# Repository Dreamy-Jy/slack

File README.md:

This is a repo containing all docs related to Slack, a custom plank style keyboard meant for being used while relaxing.

There are 2 prototype revisions planned, each one getting closer to my ideal. Experimental modules will be hosted here as well.

Any revisions pass the second revision will be for refinements.

Why are components rated differently?
- Caps have a voltage rating
- Resistor have a power dissipation rating

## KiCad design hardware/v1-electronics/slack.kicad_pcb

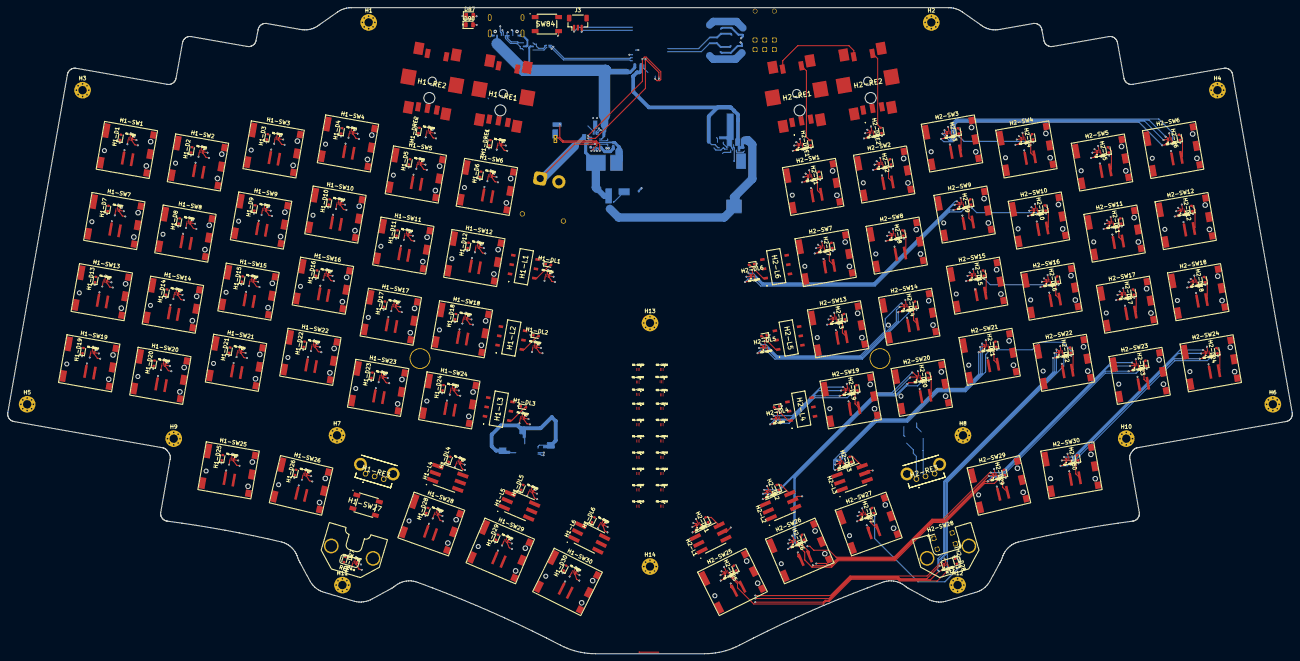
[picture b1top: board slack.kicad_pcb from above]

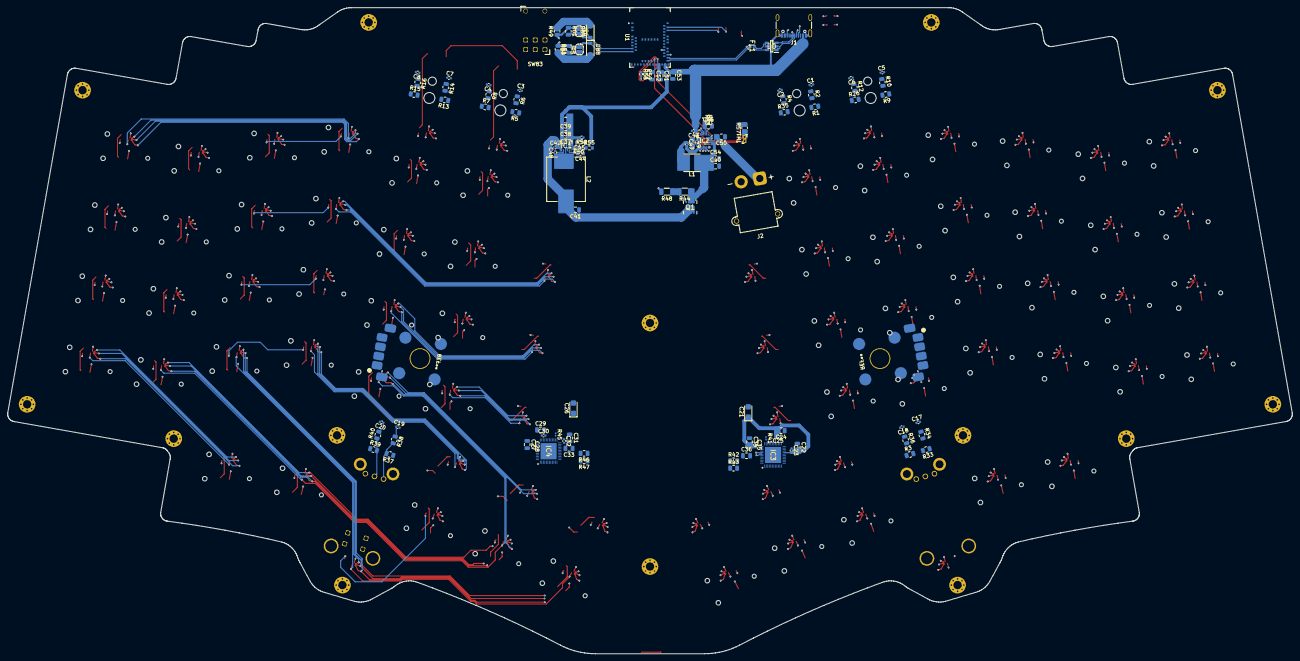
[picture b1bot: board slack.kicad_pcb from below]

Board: 4 copper layers, 338.9 x 170.4 mm, 376 parts (108 on the bottom side), 216 nets.

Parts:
C1, C2, C3, C4, C5, C6, C7, C8, C17, C18, C19, C20: 0.01μF; C_0402_1005Metric
C21, C26: 22μF; CP_EIA-3216-18_Kemet-A
C22, C24, C27, C29, C31, C33, C34, C36: 0.47μF; C_0805_2012Metric
C23, C25, C28, C30, C32, C35, C42, C48: 0.1μF; C_0402_1005Metric
C37, C38, C39, C49: 22μF; C_0805_2012Metric
C40, C41, C50, C51, C52, C53, C54: 10μF; C_0805_2012Metric
C43: 1μF; C_0402_1005Metric
C44: 2.20μF; C_0603_1608Metric
C45: 2.2nF; C_0603_1608Metric
C46: 4.7μF; C_0805_2012Metric
C47: 22nF; C_0402_1005Metric
D0: USBLC6-2SC6; SOT95P280X145-6N
D87, D90: LED_Small_Filled; LED_0805_2012Metric
D88, D89: 3.6V; D_SOD-123
FL1: EXC14CE900U
H1, H2, H3, H4, H5, H6, H7, H8, H9, H10, H11, H12, H13, H14: MountingHole_2.2mm_M2_Pad_Via
H1-D1, H1-D2, H1-D3, H1-D4, H1-D5, H1-D6, H1-D7, H1-D8, H1-D9, H1-D10, H1-D11, H1-D12, H1-D13, H1-D14, H1-D15, H1-D16, H1-D17, H1-D18, H1-D19, H1-D20, H1-D21, H1-D22, H1-D23, H1-D24, H1-D25, H1-D26, H1-D27, H1-D28, H1-D29, H1-D30, H1-DL1, H1-DL2, H1-DL3, H1-DL4, H1-DL5, H1-DL6, H1-DRE1, H1-DRE2, H2-D1, H2-D2, H2-D3, H2-D4, H2-D5, H2-D6, H2-D7, H2-D8, H2-D9, H2-D10, H2-D11, H2-D12, H2-D13, H2-D14, H2-D15, H2-D16, H2-D17, H2-D18, H2-D19, H2-D20, H2-D21, H2-D22, H2-D23, H2-D24, H2-D25, H2-D26, H2-D27, H2-D28, H2-D29, H2-D30, H2-DL1, H2-DL2, H2-DL3, H2-DL4, H2-DL5, H2-DL6, H2-DRE1, H2-DRE2: BAS16TS; D_SOD-523
H1-L1, H1-L2, H1-L3, H2-L4, H2-L5, H2-L6: SS-3235S-L3; SS3235SL3
H1-L4, H1-L5, H1-L6, H2-L1, H2-L2, H2-L3: BTSA-L-S-8
H1-LED1, H1-LED2, H1-LED3, H1-LED4, H1-LED5, H1-LED6, H1-LED7, H1-LED8, H1-LED9, H1-LED10, H1-LED11, H1-LED12, H1-LED13, H1-LED14, H1-LED15, H1-LED16, H1-LED17, H1-LED18, H1-LED19, H1-LED20, H1-LED21, H1-LED22, H1-LED23, H1-LED24, H1-LED25, H1-LED26, H1-LED27, H1-LED28, H1-LED29, H1-LED30, H1-LED31, H1-LED32, H1-LED33, H1-LED34, H1-LED35, H1-LED36, H1-LED37, H1-LED38, H1-LED39, H1-LED40, H1-LED41, H1-LED42, H1-LED43, H1-LED44, H1-LED45, H1-LED46, H1-LED47, H1-LED48, H2-LED1, H2-LED2, H2-LED3, H2-LED4, H2-LED5, H2-LED6, H2-LED7, H2-LED8, H2-LED9, H2-LED10, H2-LED11, H2-LED12, H2-LED13, H2-LED14, H2-LED15, H2-LED16, H2-LED17, H2-LED18, H2-LED19, H2-LED20, H2-LED21, H2-LED22, H2-LED23, H2-LED24, H2-LED25, H2-LED26, H2-LED27, H2-LED28, H2-LED29, H2-LED30, H2-LED31, H2-LED32, H2-LED33, H2-LED34, H2-LED35, H2-LED36, H2-LED37, H2-LED38, H2-LED39, H2-LED40, H2-LED41, H2-LED42, H2-LED43, H2-LED44, H2-LED45, H2-LED46, H2-LED47, H2-LED48: LTST-FC12WEGBD-5A; LTSTFC12WEGBD5A
H1-RE1, H1-RE2, H2-RE1, H2-RE2: PEC11S-929K-S0015; PEC11S929KS0015
H1-RE3, H2-RE3: EC10E1220505
H1-SW1, H1-SW2, H1-SW3, H1-SW4, H1-SW5, H1-SW6, H1-SW7, H1-SW8, H1-SW9, H1-SW10, H1-SW11, H1-SW12, H1-SW13, H1-SW14, H1-SW15, H1-SW16, H1-SW17, H1-SW18, H1-SW19, H1-SW20, H1-SW21, H1-SW22, H1-SW23, H1-SW24, H1-SW25, H1-SW26, H1-SW28, H1-SW29, H1-SW30, H2-SW1, H2-SW2, H2-SW3, H2-SW4, H2-SW5, H2-SW6, H2-SW7, H2-SW8, H2-SW9, H2-SW10, H2-SW11, H2-SW12, H2-SW13, H2-SW14, H2-SW15, H2-SW16, H2-SW17, H2-SW18, H2-SW19, H2-SW20, H2-SW21, H2-SW22, H2-SW23, H2-SW24, H2-SW25, H2-SW26, H2-SW27, H2-SW29, H2-SW30: MX6C-K3NB; Cherry_ULP_SMD
H1-SW27: SW_Push; SKQGAKE010
H2-SW28: SW_Push; TC-1109-C-E
IC1: TPS61288LRQQR; PTPS61288RQQR
IC2: MP2721GRH-0000-Z; QFN-22_MP2721_MNP
IC3, IC4: IS31FL3733-QFLS4-TR; QFN40P600X600X80-49N-D
J1: USB4105-GF-A-120; USB_C_Receptacle_GCT_USB4105-xx-A_16P_TopMnt_Horizontal
J2: XT30PW-M; AMASS_XT30PW-M_1x02_P2.50mm_Horizontal_Tight
J3: Female JST-SH; JST_SH_BM03B-SRSS-TB_1x03-1MP_P1.00mm_Vertical
JP5, JP6: Jumper_2_Small_Open; SolderJumper-2_P1.3mm_Open_RoundedPad1.0x1.5mm
L1: 1μH; L_Changjiang_FTC404030S
L2: 2.20μH; L_Sunlord_MWSA1005S
Q1: AON7423
R1, R2, R3, R4, R5, R6, R7, R8, R9, R10, R12, R13, R14, R15, R16, R26, R33, R34, R35, R36, R37, R38, R39, R40, R57: 10kΩ; R_0805_2012Metric
R41, R45: 22kΩ; R_0201_0603Metric
R42, R43, R46, R47: 100kΩ; R_0805_2012Metric
R44: 100kΩ; R_1206_3216Metric
R48: 1kΩ; R_1206_3216Metric
R49, R51: 5.1kΩ ≤1%; R_0805_2012Metric
R50: 22kΩ; R_0402_1005Metric
R52, R53: 1kΩ; R_01005_0402Metric
R55: 3kΩ; R_0603_1608Metric
R56: 15kΩ; R_0402_1005Metric
R58, R59: 10kΩ; R_0402_1005Metric
R60, R61: 10kΩ ≤1%; R_0805_2012Metric
SW83: 2TED3M6RES
SW84: SW_Push; SKQGAKE010
TH1: 10kΩ @ 25°C; NTCLE413E2103F102L
U1: MDBT50Q-1MV2; Raytac_MDBT50Q

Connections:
+5V: C21.1, C22.2, C23.2, C24.2, C25.2, C26.1, C27.2, C28.2, C29.2, C30.2, C31.2, C32.2, C34.2, C35.2, C37.2, C38.2, C39.2, C51.1, IC1.5 (VOUT), IC3.20 (PVCC_1), IC3.29 (PVCC_2), IC3.37 (AVCC), IC3.38 (DVCC), IC4.20 (PVCC_1), IC4.29 (PVCC_2), IC4.37 (AVCC), IC4.38 (DVCC), R50.1, U1.30 (VDDH)
/LED Matricies/Chip1CurrentSource1: H1-LED1.5 (ANODE), H1-LED2.5 (ANODE), H1-LED3.5 (ANODE), IC3.16 (CS1)
/LED Matricies/Chip1CurrentSource2: H1-LED4.5 (ANODE), H1-LED5.5 (ANODE), H1-LED6.5 (ANODE), IC3.17 (CS2)
/LED Matricies/Chip1CurrentSource3: H1-LED7.5 (ANODE), H1-LED8.5 (ANODE), H1-LED9.5 (ANODE), IC3.18 (CS3)
/LED Matricies/Chip1CurrentSource4: H1-LED10.5 (ANODE), H1-LED11.5 (ANODE), H1-LED12.5 (ANODE), IC3.19 (CS4)
/LED Matricies/Chip1CurrentSource5: H1-LED13.5 (ANODE), H1-LED14.5 (ANODE), H1-LED15.5 (ANODE), IC3.21 (CS5)
/LED Matricies/Chip1CurrentSource6: H1-LED16.5 (ANODE), H1-LED17.5 (ANODE), H1-LED18.5 (ANODE), IC3.22 (CS6)
/LED Matricies/Chip1CurrentSource7: H1-LED19.5 (ANODE), H1-LED20.5 (ANODE), H1-LED21.5 (ANODE), IC3.23 (CS7)
/LED Matricies/Chip1CurrentSource8: H1-LED22.5 (ANODE), H1-LED23.5 (ANODE), H1-LED24.5 (ANODE), IC3.24 (CS8)
/LED Matricies/Chip1CurrentSource9: H1-LED25.5 (ANODE), H1-LED26.5 (ANODE), H1-LED27.5 (ANODE), IC3.25 (CS9)
/LED Matricies/Chip1CurrentSource10: H1-LED28.5 (ANODE), H1-LED29.5 (ANODE), H1-LED30.5 (ANODE), IC3.26 (CS10)
/LED Matricies/Chip1CurrentSource11: H1-LED31.5 (ANODE), H1-LED32.5 (ANODE), H1-LED33.5 (ANODE), IC3.27 (CS11)
/LED Matricies/Chip1CurrentSource12: H1-LED34.5 (ANODE), H1-LED35.5 (ANODE), H1-LED36.5 (ANODE), IC3.28 (CS12)
/LED Matricies/Chip1CurrentSource13: H1-LED37.5 (ANODE), H1-LED38.5 (ANODE), H1-LED39.5 (ANODE), IC3.30 (CS13)
/LED Matricies/Chip1CurrentSource14: H1-LED40.5 (ANODE), H1-LED41.5 (ANODE), H1-LED42.5 (ANODE), IC3.31 (CS14)
/LED Matricies/Chip1CurrentSource15: H1-LED43.5 (ANODE), H1-LED44.5 (ANODE), H1-LED45.5 (ANODE), IC3.32 (CS15)
/LED Matricies/Chip1CurrentSource16: H1-LED46.5 (ANODE), H1-LED47.5 (ANODE), H1-LED48.5 (ANODE), IC3.33 (CS16)
/LED Matricies/Chip1I2C_Reset: IC3.47 (IICRST), R43.2
/LED Matricies/Chip1Shutdown: IC3.46 (SDB), R42.2, U1.36 (P0.14)
/LED Matricies/Chip1SinkSwitch1: H1-LED1.1 (BLUE), H1-LED4.1 (BLUE), H1-LED7.1 (BLUE), H1-LED10.1 (BLUE), H1-LED13.1 (BLUE), H1-LED16.1 (BLUE), H1-LED19.1 (BLUE), H1-LED22.1 (BLUE), H1-LED25.1 (BLUE), H1-LED28.1 (BLUE), H1-LED31.1 (BLUE), H1-LED34.1 (BLUE), H1-LED37.1 (BLUE), H1-LED40.1 (BLUE), H1-LED43.1 (BLUE), H1-LED46.1 (BLUE), IC3.2 (SW1)
/LED Matricies/Chip1SinkSwitch2: H1-LED1.2 (GREEN), H1-LED4.2 (GREEN), H1-LED7.2 (GREEN), H1-LED10.2 (GREEN), H1-LED13.2 (GREEN), H1-LED16.2 (GREEN), H1-LED19.2 (GREEN), H1-LED22.2 (GREEN), H1-LED25.2 (GREEN), H1-LED28.2 (GREEN), H1-LED31.2 (GREEN), H1-LED34.2 (GREEN), H1-LED37.2 (GREEN), H1-LED40.2 (GREEN), H1-LED43.2 (GREEN), H1-LED46.2 (GREEN), IC3.3 (SW2)
/LED Matricies/Chip1SinkSwitch3: H1-LED1.3 (RED), H1-LED4.3 (RED), H1-LED7.3 (RED), H1-LED10.3 (RED), H1-LED13.3 (RED), H1-LED16.3 (RED), H1-LED19.3 (RED), H1-LED22.3 (RED), H1-LED25.3 (RED), H1-LED28.3 (RED), H1-LED31.3 (RED), H1-LED34.3 (RED), H1-LED37.3 (RED), H1-LED40.3 (RED), H1-LED43.3 (RED), H1-LED46.3 (RED), IC3.4 (SW3)
/LED Matricies/Chip1SinkSwitch4: H1-LED1.4 (WHITE), H1-LED4.4 (WHITE), H1-LED7.4 (WHITE), H1-LED10.4 (WHITE), H1-LED13.4 (WHITE), H1-LED16.4 (WHITE), H1-LED19.4 (WHITE), H1-LED22.4 (WHITE), H1-LED25.4 (WHITE), H1-LED28.4 (WHITE), H1-LED31.4 (WHITE), H1-LED34.4 (WHITE), H1-LED37.4 (WHITE), H1-LED40.4 (WHITE), H1-LED43.4 (WHITE), H1-LED46.4 (WHITE), IC3.6 (SW4)
/LED Matricies/Chip1SinkSwitch5: H1-LED2.1 (BLUE), H1-LED5.1 (BLUE), H1-LED8.1 (BLUE), H1-LED11.1 (BLUE), H1-LED14.1 (BLUE), H1-LED17.1 (BLUE), H1-LED20.1 (BLUE), H1-LED23.1 (BLUE), H1-LED26.1 (BLUE), H1-LED29.1 (BLUE), H1-LED32.1 (BLUE), H1-LED35.1 (BLUE), H1-LED38.1 (BLUE), H1-LED41.1 (BLUE), H1-LED44.1 (BLUE), H1-LED47.1 (BLUE), IC3.7 (SW5)
/LED Matricies/Chip1SinkSwitch6: H1-LED2.2 (GREEN), H1-LED5.2 (GREEN), H1-LED8.2 (GREEN), H1-LED11.2 (GREEN), H1-LED14.2 (GREEN), H1-LED17.2 (GREEN), H1-LED20.2 (GREEN), H1-LED23.2 (GREEN), H1-LED26.2 (GREEN), H1-LED29.2 (GREEN), H1-LED32.2 (GREEN), H1-LED35.2 (GREEN), H1-LED38.2 (GREEN), H1-LED41.2 (GREEN), H1-LED44.2 (GREEN), H1-LED47.2 (GREEN), IC3.8 (SW6)
/LED Matricies/Chip1SinkSwitch7: H1-LED2.3 (RED), H1-LED5.3 (RED), H1-LED8.3 (RED), H1-LED11.3 (RED), H1-LED14.3 (RED), H1-LED17.3 (RED), H1-LED20.3 (RED), H1-LED23.3 (RED), H1-LED26.3 (RED), H1-LED29.3 (RED), H1-LED32.3 (RED), H1-LED35.3 (RED), H1-LED38.3 (RED), H1-LED41.3 (RED), H1-LED44.3 (RED), H1-LED47.3 (RED), IC3.9 (SW7)
/LED Matricies/Chip1SinkSwitch8: H1-LED2.4 (WHITE), H1-LED5.4 (WHITE), H1-LED8.4 (WHITE), H1-LED11.4 (WHITE), H1-LED14.4 (WHITE), H1-LED17.4 (WHITE), H1-LED20.4 (WHITE), H1-LED23.4 (WHITE), H1-LED26.4 (WHITE), H1-LED29.4 (WHITE), H1-LED32.4 (WHITE), H1-LED35.4 (WHITE), H1-LED38.4 (WHITE), H1-LED41.4 (WHITE), H1-LED44.4 (WHITE), H1-LED47.4 (WHITE), IC3.10 (SW8)
/LED Matricies/Chip1SinkSwitch9: H1-LED3.1 (BLUE), H1-LED6.1 (BLUE), H1-LED9.1 (BLUE), H1-LED12.1 (BLUE), H1-LED15.1 (BLUE), H1-LED18.1 (BLUE), H1-LED21.1 (BLUE), H1-LED24.1 (BLUE), H1-LED27.1 (BLUE), H1-LED30.1 (BLUE), H1-LED33.1 (BLUE), H1-LED36.1 (BLUE), H1-LED39.1 (BLUE), H1-LED42.1 (BLUE), H1-LED45.1 (BLUE), H1-LED48.1 (BLUE), IC3.11 (SW9)
/LED Matricies/Chip1SinkSwitch10: H1-LED3.2 (GREEN), H1-LED6.2 (GREEN), H1-LED9.2 (GREEN), H1-LED12.2 (GREEN), H1-LED15.2 (GREEN), H1-LED18.2 (GREEN), H1-LED21.2 (GREEN), H1-LED24.2 (GREEN), H1-LED27.2 (GREEN), H1-LED30.2 (GREEN), H1-LED33.2 (GREEN), H1-LED36.2 (GREEN), H1-LED39.2 (GREEN), H1-LED42.2 (GREEN), H1-LED45.2 (GREEN), H1-LED48.2 (GREEN), IC3.13 (SW10)
/LED Matricies/Chip1SinkSwitch11: H1-LED3.3 (RED), H1-LED6.3 (RED), H1-LED9.3 (RED), H1-LED12.3 (RED), H1-LED15.3 (RED), H1-LED18.3 (RED), H1-LED21.3 (RED), H1-LED24.3 (RED), H1-LED27.3 (RED), H1-LED30.3 (RED), H1-LED33.3 (RED), H1-LED36.3 (RED), H1-LED39.3 (RED), H1-LED42.3 (RED), H1-LED45.3 (RED), H1-LED48.3 (RED), IC3.14 (SW11)
/LED Matricies/Chip1SinkSwitch12: H1-LED3.4 (WHITE), H1-LED6.4 (WHITE), H1-LED9.4 (WHITE), H1-LED12.4 (WHITE), H1-LED15.4 (WHITE), H1-LED18.4 (WHITE), H1-LED21.4 (WHITE), H1-LED24.4 (WHITE), H1-LED27.4 (WHITE), H1-LED30.4 (WHITE), H1-LED33.4 (WHITE), H1-LED36.4 (WHITE), H1-LED39.4 (WHITE), H1-LED42.4 (WHITE), H1-LED45.4 (WHITE), H1-LED48.4 (WHITE), IC3.15 (SW12)
/LED Matricies/Chip2CurrentSource1: H2-LED1.5 (ANODE), H2-LED2.5 (ANODE), H2-LED3.5 (ANODE), IC4.16 (CS1)
/LED Matricies/Chip2CurrentSource2: H2-LED4.5 (ANODE), H2-LED5.5 (ANODE), H2-LED6.5 (ANODE), IC4.17 (CS2)
/LED Matricies/Chip2CurrentSource3: H2-LED7.5 (ANODE), H2-LED8.5 (ANODE), H2-LED9.5 (ANODE), IC4.18 (CS3)
/LED Matricies/Chip2CurrentSource4: H2-LED10.5 (ANODE), H2-LED11.5 (ANODE), H2-LED12.5 (ANODE), IC4.19 (CS4)
/LED Matricies/Chip2CurrentSource5: H2-LED13.5 (ANODE), H2-LED14.5 (ANODE), H2-LED15.5 (ANODE), IC4.21 (CS5)
/LED Matricies/Chip2CurrentSource6: H2-LED16.5 (ANODE), H2-LED17.5 (ANODE), H2-LED18.5 (ANODE), IC4.22 (CS6)
/LED Matricies/Chip2CurrentSource7: H2-LED19.5 (ANODE), H2-LED20.5 (ANODE), H2-LED21.5 (ANODE), IC4.23 (CS7)
/LED Matricies/Chip2CurrentSource8: H2-LED22.5 (ANODE), H2-LED23.5 (ANODE), H2-LED24.5 (ANODE), IC4.24 (CS8)
/LED Matricies/Chip2CurrentSource9: H2-LED25.5 (ANODE), H2-LED26.5 (ANODE), H2-LED27.5 (ANODE), IC4.25 (CS9)
/LED Matricies/Chip2CurrentSource10: H2-LED28.5 (ANODE), H2-LED29.5 (ANODE), H2-LED30.5 (ANODE), IC4.26 (CS10)
/LED Matricies/Chip2CurrentSource11: H2-LED31.5 (ANODE), H2-LED32.5 (ANODE), H2-LED33.5 (ANODE), IC4.27 (CS11)
/LED Matricies/Chip2CurrentSource12: H2-LED34.5 (ANODE), H2-LED35.5 (ANODE), H2-LED36.5 (ANODE), IC4.28 (CS12)
/LED Matricies/Chip2CurrentSource13: H2-LED37.5 (ANODE), H2-LED38.5 (ANODE), H2-LED39.5 (ANODE), IC4.30 (CS13)
/LED Matricies/Chip2CurrentSource14: H2-LED40.5 (ANODE), H2-LED41.5 (ANODE), H2-LED42.5 (ANODE), IC4.31 (CS14)
/LED Matricies/Chip2CurrentSource15: H2-LED43.5 (ANODE), H2-LED44.5 (ANODE), H2-LED45.5 (ANODE), IC4.32 (CS15)
/LED Matricies/Chip2CurrentSource16: H2-LED46.5 (ANODE), H2-LED47.5 (ANODE), H2-LED48.5 (ANODE), IC4.33 (CS16)
/LED Matricies/Chip2I2C_Reset: IC4.47 (IICRST), R47.2
/LED Matricies/Chip2Shutdown: IC4.46 (SDB), R46.2, U1.19 (P0.26)
/LED Matricies/Chip2SinkSwitch1: H2-LED1.1 (BLUE), H2-LED4.1 (BLUE), H2-LED7.1 (BLUE), H2-LED10.1 (BLUE), H2-LED13.1 (BLUE), H2-LED16.1 (BLUE), H2-LED19.1 (BLUE), H2-LED22.1 (BLUE), H2-LED25.1 (BLUE), H2-LED28.1 (BLUE), H2-LED31.1 (BLUE), H2-LED34.1 (BLUE), H2-LED37.1 (BLUE), H2-LED40.1 (BLUE), H2-LED43.1 (BLUE), H2-LED46.1 (BLUE), IC4.2 (SW1)
/LED Matricies/Chip2SinkSwitch2: H2-LED1.2 (GREEN), H2-LED4.2 (GREEN), H2-LED7.2 (GREEN), H2-LED10.2 (GREEN), H2-LED13.2 (GREEN), H2-LED16.2 (GREEN), H2-LED19.2 (GREEN), H2-LED22.2 (GREEN), H2-LED25.2 (GREEN), H2-LED28.2 (GREEN), H2-LED31.2 (GREEN), H2-LED34.2 (GREEN), H2-LED37.2 (GREEN), H2-LED40.2 (GREEN), H2-LED43.2 (GREEN), H2-LED46.2 (GREEN), IC4.3 (SW2)
/LED Matricies/Chip2SinkSwitch3: H2-LED1.3 (RED), H2-LED4.3 (RED), H2-LED7.3 (RED), H2-LED10.3 (RED), H2-LED13.3 (RED), H2-LED16.3 (RED), H2-LED19.3 (RED), H2-LED22.3 (RED), H2-LED25.3 (RED), H2-LED28.3 (RED), H2-LED31.3 (RED), H2-LED34.3 (RED), H2-LED37.3 (RED), H2-LED40.3 (RED), H2-LED43.3 (RED), H2-LED46.3 (RED), IC4.4 (SW3)
/LED Matricies/Chip2SinkSwitch4: H2-LED1.4 (WHITE), H2-LED4.4 (WHITE), H2-LED7.4 (WHITE), H2-LED10.4 (WHITE), H2-LED13.4 (WHITE), H2-LED16.4 (WHITE), H2-LED19.4 (WHITE), H2-LED22.4 (WHITE), H2-LED25.4 (WHITE), H2-LED28.4 (WHITE), H2-LED31.4 (WHITE), H2-LED34.4 (WHITE), H2-LED37.4 (WHITE), H2-LED40.4 (WHITE), H2-LED43.4 (WHITE), H2-LED46.4 (WHITE), IC4.6 (SW4)
/LED Matricies/Chip2SinkSwitch5: H2-LED2.1 (BLUE), H2-LED5.1 (BLUE), H2-LED8.1 (BLUE), H2-LED11.1 (BLUE), H2-LED14.1 (BLUE), H2-LED17.1 (BLUE), H2-LED20.1 (BLUE), H2-LED23.1 (BLUE), H2-LED26.1 (BLUE), H2-LED29.1 (BLUE), H2-LED32.1 (BLUE), H2-LED35.1 (BLUE), H2-LED38.1 (BLUE), H2-LED41.1 (BLUE), H2-LED44.1 (BLUE), H2-LED47.1 (BLUE), IC4.7 (SW5)
/LED Matricies/Chip2SinkSwitch6: H2-LED2.2 (GREEN), H2-LED5.2 (GREEN), H2-LED8.2 (GREEN), H2-LED11.2 (GREEN), H2-LED14.2 (GREEN), H2-LED17.2 (GREEN), H2-LED20.2 (GREEN), H2-LED23.2 (GREEN), H2-LED26.2 (GREEN), H2-LED29.2 (GREEN), H2-LED32.2 (GREEN), H2-LED35.2 (GREEN), H2-LED38.2 (GREEN), H2-LED41.2 (GREEN), H2-LED44.2 (GREEN), H2-LED47.2 (GREEN), IC4.8 (SW6)
/LED Matricies/Chip2SinkSwitch7: H2-LED2.3 (RED), H2-LED5.3 (RED), H2-LED8.3 (RED), H2-LED11.3 (RED), H2-LED14.3 (RED), H2-LED17.3 (RED), H2-LED20.3 (RED), H2-LED23.3 (RED), H2-LED26.3 (RED), H2-LED29.3 (RED), H2-LED32.3 (RED), H2-LED35.3 (RED), H2-LED38.3 (RED), H2-LED41.3 (RED), H2-LED44.3 (RED), H2-LED47.3 (RED), IC4.9 (SW7)
/LED Matricies/Chip2SinkSwitch8: H2-LED2.4 (WHITE), H2-LED5.4 (WHITE), H2-LED8.4 (WHITE), H2-LED11.4 (WHITE), H2-LED14.4 (WHITE), H2-LED17.4 (WHITE), H2-LED20.4 (WHITE), H2-LED23.4 (WHITE), H2-LED26.4 (WHITE), H2-LED29.4 (WHITE), H2-LED32.4 (WHITE), H2-LED35.4 (WHITE), H2-LED38.4 (WHITE), H2-LED41.4 (WHITE), H2-LED44.4 (WHITE), H2-LED47.4 (WHITE), IC4.10 (SW8)
/LED Matricies/Chip2SinkSwitch9: H2-LED3.1 (BLUE), H2-LED6.1 (BLUE), H2-LED9.1 (BLUE), H2-LED12.1 (BLUE), H2-LED15.1 (BLUE), H2-LED18.1 (BLUE), H2-LED21.1 (BLUE), H2-LED24.1 (BLUE), H2-LED27.1 (BLUE), H2-LED30.1 (BLUE), H2-LED33.1 (BLUE), H2-LED36.1 (BLUE), H2-LED39.1 (BLUE), H2-LED42.1 (BLUE), H2-LED45.1 (BLUE), H2-LED48.1 (BLUE), IC4.11 (SW9)
/LED Matricies/Chip2SinkSwitch10: H2-LED3.2 (GREEN), H2-LED6.2 (GREEN), H2-LED9.2 (GREEN), H2-LED12.2 (GREEN), H2-LED15.2 (GREEN), H2-LED18.2 (GREEN), H2-LED21.2 (GREEN), H2-LED24.2 (GREEN), H2-LED27.2 (GREEN), H2-LED30.2 (GREEN), H2-LED33.2 (GREEN), H2-LED36.2 (GREEN), H2-LED39.2 (GREEN), H2-LED42.2 (GREEN), H2-LED45.2 (GREEN), H2-LED48.2 (GREEN), IC4.13 (SW10)
/LED Matricies/Chip2SinkSwitch11: H2-LED3.3 (RED), H2-LED6.3 (RED), H2-LED9.3 (RED), H2-LED12.3 (RED), H2-LED15.3 (RED), H2-LED18.3 (RED), H2-LED21.3 (RED), H2-LED24.3 (RED), H2-LED27.3 (RED), H2-LED30.3 (RED), H2-LED33.3 (RED), H2-LED36.3 (RED), H2-LED39.3 (RED), H2-LED42.3 (RED), H2-LED45.3 (RED), H2-LED48.3 (RED), IC4.14 (SW11)
/LED Matricies/Chip2SinkSwitch12: H2-LED3.4 (WHITE), H2-LED6.4 (WHITE), H2-LED9.4 (WHITE), H2-LED12.4 (WHITE), H2-LED15.4 (WHITE), H2-LED18.4 (WHITE), H2-LED21.4 (WHITE), H2-LED24.4 (WHITE), H2-LED27.4 (WHITE), H2-LED30.4 (WHITE), H2-LED33.4 (WHITE), H2-LED36.4 (WHITE), H2-LED39.4 (WHITE), H2-LED42.4 (WHITE), H2-LED45.4 (WHITE), H2-LED48.4 (WHITE), IC4.15 (SW12)
/LED Matricies/I2C1.SCL: IC2.16 (SCL), IC3.42 (SCL), IC4.42 (SCL), IC4.44 (ADDR2), R59.2, U1.29 (P0.12)
/LED Matricies/I2C1.SDA: IC2.15 (SDA), IC3.41 (SDA), IC4.41 (SDA), R58.2, U1.27 (P0.11)
/LED Matricies/LED Matrix Controller 1/R_EXT: IC3.35 (R_EXT), R41.2
/LED Matricies/LED Matrix Controller 2/R_EXT: IC4.35 (R_EXT), R45.2
/LED Matricies/Sync: IC3.40 (SYNC), IC4.40 (SYNC)
/LED Matricies/~Chip1Interrupt: IC3.45 (~INTB), U1.24 (P0.08)
/LED Matricies/~Chip2Interrupt: IC4.45 (~INTB), U1.23 (P0.07)
/MCU/Column1: H1-L1.2 (COM_1), H1-L1.5 (COM_2), H1-SW1.1, H1-SW7.1, H1-SW13.1, H1-SW19.1, H1-SW25.1, U1.42 (P0.19)
/MCU/Column2: H1-L2.2 (COM_1), H1-L2.5 (COM_2), H1-SW2.1, H1-SW8.1, H1-SW14.1, H1-SW20.1, H1-SW26.1, U1.43 (P0.21)
/MCU/Column3: H1-L3.2 (COM_1), H1-L3.5 (COM_2), H1-SW3.1, H1-SW9.1, H1-SW15.1, H1-SW21.1, H1-SW27.1, U1.44 (P0.20)
/MCU/Column4: H1-L4.2, H1-L4.5 (2), H1-SW4.1, H1-SW10.1, H1-SW16.1, H1-SW22.1, H1-SW28.1, U1.41 (P0.17)
/MCU/Column5: H1-L5.2, H1-L5.5 (2), H1-SW5.1, H1-SW11.1, H1-SW17.1, H1-SW23.1, H1-SW29.1, U1.39 (P0.15)
/MCU/Column6: H1-L6.2, H1-L6.5 (2), H1-SW6.1, H1-SW12.1, H1-SW18.1, H1-SW24.1, H1-SW30.1, U1.38 (P0.16)
/MCU/Column7: H1-RE1.D1 (SI), H1-RE2.D1 (SI), U1.49 (P0.25)
/MCU/Column8: H2-RE1.D1 (SI), H2-RE2.D1 (SI), U1.3 (P1.10)
/MCU/Column9: H2-L1.2, H2-L1.5 (2), H2-SW1.1, H2-SW7.1, H2-SW13.1, H2-SW19.1, H2-SW25.1, U1.16 (P0.27)
/MCU/Column10: H2-L2.2, H2-L2.5 (2), H2-SW2.1, H2-SW8.1, H2-SW14.1, H2-SW20.1, H2-SW26.1, U1.13 (P0.28)
/MCU/Column11: H2-L3.2, H2-L3.5 (2), H2-SW3.1, H2-SW9.1, H2-SW15.1, H2-SW21.1, H2-SW27.1, U1.11 (P0.02)
/MCU/Column12: H2-L4.2 (COM_1), H2-L4.5 (COM_2), H2-SW4.1, H2-SW10.1, H2-SW16.1, H2-SW22.1, H2-SW28.1, U1.8 (P1.15)
/MCU/Column13: H2-L5.2 (COM_1), H2-L5.5 (COM_2), H2-SW5.1, H2-SW11.1, H2-SW17.1, H2-SW23.1, H2-SW29.1, U1.9 (P0.03)
/MCU/Column14: H2-L6.2 (COM_1), H2-L6.5 (COM_2), H2-SW6.1, H2-SW12.1, H2-SW18.1, H2-SW24.1, H2-SW30.1, U1.10 (AIN5)
/MCU/RESET: SW84.2, U1.40 (P0.18)
/MCU/RotaryEncoder_AChannel1: C1.1, R2.1, U1.47 (P1.00)
/MCU/RotaryEncoder_AChannel2: C3.1, R6.1, U1.4 (P1.11)
/MCU/RotaryEncoder_AChannel3: C5.1, R10.2, U1.45 (P0.23)
/MCU/RotaryEncoder_AChannel4: C7.1, R14.2, U1.6 (P1.13)
/MCU/RotaryEncoder_AChannel5: C17.1, R34.1, U1.26 (P1.09)
/MCU/RotaryEncoder_AChannel6: C19.1, R38.1, U1.22 (P0.06)
/MCU/RotaryEncoder_BChannel1: C2.1, R4.1, U1.48 (P0.24)
/MCU/RotaryEncoder_BChannel2: C4.1, R8.1, U1.5 (P1.12)
/MCU/RotaryEncoder_BChannel3: C6.1, R12.1, U1.46 (P0.22)
/MCU/RotaryEncoder_BChannel4: C8.1, R16.1, U1.7 (P1.14)
/MCU/RotaryEncoder_BChannel5: C18.1, R36.1, U1.25 (P1.08)
/MCU/RotaryEncoder_BChannel6: C20.1, R40.2, U1.20 (P0.04)
/MCU/Row1: H1-DL1.1 (K_1), H1-DL2.1 (K_1), H1-DL3.1 (K_1), H1-DL4.1 (K), H1-DL5.1 (K), H1-DL6.1 (K), H2-DL1.1 (K), H2-DL2.1 (K), H2-DL3.1 (K), H2-DL4.1 (K_1), H2-DL5.1 (K_1), H2-DL6.1 (K_1), U1.58 (P1.07)
/MCU/Row2: H1-D1.1 (K), H1-D2.1 (K), H1-D3.1 (K), H1-D4.1 (K), H1-D5.1 (K), H1-D6.1 (K), H1-DRE1.1 (K), H2-D1.1 (K), H2-D2.1 (K), H2-D3.1 (K), H2-D4.1 (K), H2-D5.1 (K), H2-D6.1 (K), H2-DRE1.1 (K), U1.56 (P1.04)
/MCU/Row3: H1-D7.1 (K), H1-D8.1 (K), H1-D9.1 (K), H1-D10.1 (K), H1-D11.1 (K), H1-D12.1 (K), H1-DRE2.1 (K), H2-D7.1 (K), H2-D8.1 (K), H2-D9.1 (K), H2-D10.1 (K), H2-D11.1 (K), H2-D12.1 (K), H2-DRE2.1 (K), U1.57 (P1.06)
/MCU/Row4: H1-D13.1 (K), H1-D14.1 (K), H1-D15.1 (K), H1-D16.1 (K), H1-D17.1 (K), H1-D18.1 (K), H2-D13.1 (K), H2-D14.1 (K), H2-D15.1 (K), H2-D16.1 (K), H2-D17.1 (K), H2-D18.1 (K), U1.59 (P1.05)
/MCU/Row5: H1-D19.1 (K), H1-D20.1 (K), H1-D21.1 (K), H1-D22.1 (K), H1-D23.1 (K), H1-D24.1 (K), H2-D19.1 (K), H2-D20.1 (K), H2-D21.1 (K), H2-D22.1 (K), H2-D23.1 (K), H2-D24.1 (K), U1.60 (P1.03)
/MCU/Row6: H1-D25.1 (K), H1-D26.1 (K), H1-D27.1 (K), H1-D28.1 (K), H1-D29.1 (K), H1-D30.1 (K), H2-D25.1 (K), H2-D26.1 (K), H2-D27.1 (K), H2-D28.1 (K), H2-D29.1 (K), H2-D30.1 (K), U1.61 (P1.01)
/MCU/SWDCLK: J3.1, U1.53 (SWDCLK)
/MCU/SWDIO: J3.3, U1.51 (SWDIO)
/MCU/USB.CC1: D88.1 (K), JP5.2 (B), R60.2, U1.14 (AIN6)
/MCU/USB.CC2: D89.1 (K), JP6.2 (B), R61.2, U1.12 (AIN7)
/MCU/USB.D+: D0.3 (I/O2), D0.4 (I/O2), FL1.1, FL1.4, IC2.21 (D+), J1.A7 (D-), J1.B7 (D-), U1.35 (D+)
/MCU/USB.D-: D0.1 (I/O1), D0.6 (I/O1), FL1.2, FL1.3, IC2.20 (D-), J1.A6 (D+), J1.B6 (D+), U1.34 (D-)
/MCU/~ChargingChipInterrupt: IC2.8 (~INT), U1.37 (P0.13)
/Power Train/BATT: C50.1, IC2.12 (BATTSNS), IC2.14 (BATT), J2.1
/Power Train/BST_MP: C47.2, IC2.6 (BST)
/Power Train/BST_TPS: C48.2, IC1.8 (BST)
/Power Train/CC1: J1.A5 (CC1), JP5.1 (A), R51.1, R60.1
/Power Train/CC2: J1.B5 (CC2), JP6.1 (A), R49.1, R61.1
/Power Train/COMP: C45.2, IC1.2 (COMP)
/Power Train/FB: IC1.1 (FB), R50.2, R55.1
/Power Train/NCT1: IC2.10 (NTC1), R57.1, TH1.2
/Power Train/PG/NTC2: D87.1 (K), IC2.9 (PG/NTC2)
/Power Train/PMID: C49.1, IC2.3 (PMID)
/Power Train/STAT/IB: D90.1 (K), IC2.11 (STAT/IB)
/Power Train/SW_MP: C47.1, IC2.4 (SW), L1.2
/Power Train/SW_TPS: C48.1, IC1.4 (SW), IC1.9 (SW), L2.1
DGND: C1.2, C2.2, C3.2, C4.2, C5.2, C6.2, C7.2, C8.2, C17.2, C18.2, C19.2, C20.2, C21.2, C22.1, C23.1, C24.1, C25.1, C26.2, C27.1, C28.1, C29.1, C30.1, C31.1, C32.1, C33.1, C34.1, C35.1, C36.1, C37.1, C38.1, C39.1, C40.2, C41.1, C42.1, C43.2, C44.1, C46.2, C49.2, C50.2, C51.2, C52.2, C53.2, C54.2, D0.2 (GND), D88.2 (A), D89.2 (A), H1.1, H1-RE1.C1 (C), H1-RE1.MP1 (H), H1-RE1.MP2 (H), H1-RE1.MP3 (H), H1-RE1.MP4 (H), H1-RE1.MP5 (H), H1-RE1.MP6 (H), H1-RE2.C1 (C), H1-RE2.MP1 (H), H1-RE2.MP2 (H), H1-RE2.MP3 (H), H1-RE2.MP4 (H), H1-RE2.MP5 (H), H1-RE2.MP6 (H), H1-RE3.C1 (C), H1-RE3.MH1 (H), H1-RE3.MH2 (H), H2.1, H2-RE1.C1 (C), H2-RE1.MP1 (H), H2-RE1.MP2 (H), H2-RE1.MP3 (H), H2-RE1.MP4 (H), H2-RE1.MP5 (H), H2-RE1.MP6 (H), H2-RE2.C1 (C), H2-RE2.MP1 (H), H2-RE2.MP2 (H), H2-RE2.MP3 (H), H2-RE2.MP4 (H), H2-RE2.MP5 (H), H2-RE2.MP6 (H), H2-RE3.C1 (C), H2-RE3.MH1 (H), H2-RE3.MH2 (H), H3.1, H4.1, H5.1, H6.1, H7.1, H8.1, H9.1, H10.1, H11.1, H12.1, H13.1, H14.1, IC1.3 (PGND), IC1.10 (AGND), IC2.5 (PGND), IC2.18 (AGND), IC3.5 (PGND_1), IC3.12 (PGND_2), IC3.34 (AGND), IC3.43 (ADDR1), IC3.44 (ADDR2), IC3.48 (GND), IC3.49 (EP), IC4.5 (PGND_1), IC4.12 (PGND_2), IC4.34 (AGND), IC4.43 (ADDR1), IC4.48 (GND), IC4.49 (EP), J1.A1 (GND), J1.A12 (GND), J1.B1 (GND), J1.B12 (GND), J1.SH (SHIELD), J2.2, J2.MP (MountPin), J3.2, J3.MP (MountPin), R41.1, R42.1, R43.1, R45.1, R46.1, R47.1, R49.2, R51.2, R55.2, R56.2, SW83.1 (A), SW83.4 (A), SW84.1, TH1.1, U1.1 (GND), U1.2 (GND), U1.15 (GND), U1.33 (GND), U1.55 (GND)
unnamed: C45.1, R56.1
unnamed: D87.2 (A), R53.1
unnamed: D90.2 (A), R52.1
unnamed: H1-D1.2 (A), H1-SW1.2
unnamed: H1-D2.2 (A), H1-SW2.2
unnamed: H1-D3.2 (A), H1-SW3.2
unnamed: H1-D4.2 (A), H1-SW4.2
unnamed: H1-D5.2 (A), H1-SW5.2
unnamed: H1-D6.2 (A), H1-SW6.2
unnamed: H1-D7.2 (A), H1-SW7.2
unnamed: H1-D8.2 (A), H1-SW8.2
unnamed: H1-D9.2 (A), H1-SW9.2
unnamed: H1-D10.2 (A), H1-SW10.2
unnamed: H1-D11.2 (A), H1-SW11.2
unnamed: H1-D12.2 (A), H1-SW12.2
unnamed: H1-D13.2 (A), H1-SW13.2
unnamed: H1-D14.2 (A), H1-SW14.2
unnamed: H1-D15.2 (A), H1-SW15.2
unnamed: H1-D16.2 (A), H1-SW16.2
unnamed: H1-D17.2 (A), H1-SW17.2
unnamed: H1-D18.2 (A), H1-SW18.2
unnamed: H1-D19.2 (A), H1-SW19.2
unnamed: H1-D20.2 (A), H1-SW20.2
unnamed: H1-D21.2 (A), H1-SW21.2
unnamed: H1-D22.2 (A), H1-SW22.2
unnamed: H1-D23.2 (A), H1-SW23.2
unnamed: H1-D24.2 (A), H1-SW24.2
unnamed: H1-D25.2 (A), H1-SW25.2
unnamed: H1-D26.2 (A), H1-SW26.2
unnamed: H1-D27.2 (A), H1-SW27.2
unnamed: H1-D28.2 (A), H1-SW28.2
unnamed: H1-D29.2 (A), H1-SW29.2
unnamed: H1-D30.2 (A), H1-SW30.2
unnamed: H1-DL4.2 (A), H1-L4.3, H1-L4.6 (3)
unnamed: H1-DL5.2 (A), H1-L5.3, H1-L5.6 (3)
unnamed: H1-DL6.2 (A), H1-L6.3, H1-L6.6 (3)
unnamed: H1-DRE1.2 (A), H1-RE1.E1 (SO)
unnamed: H1-DRE2.2 (A), H1-RE2.E1 (SO)
unnamed: H1-RE1.A1 (A), R1.2, R2.2
unnamed: H1-RE1.B1 (B), R4.2, R35.2
unnamed: H1-RE2.A1 (A), R9.2, R10.1
unnamed: H1-RE2.B1 (B), R12.2, R26.1
unnamed: H1-RE3.A1 (A), R33.2, R34.2
unnamed: H1-RE3.B1 (B), R3.2, R36.2
unnamed: H2-D1.2 (A), H2-SW1.2
unnamed: H2-D2.2 (A), H2-SW2.2
unnamed: H2-D3.2 (A), H2-SW3.2
unnamed: H2-D4.2 (A), H2-SW4.2
unnamed: H2-D5.2 (A), H2-SW5.2
unnamed: H2-D6.2 (A), H2-SW6.2
unnamed: H2-D7.2 (A), H2-SW7.2
unnamed: H2-D8.2 (A), H2-SW8.2
unnamed: H2-D9.2 (A), H2-SW9.2
unnamed: H2-D10.2 (A), H2-SW10.2
unnamed: H2-D11.2 (A), H2-SW11.2
unnamed: H2-D12.2 (A), H2-SW12.2
unnamed: H2-D13.2 (A), H2-SW13.2
unnamed: H2-D14.2 (A), H2-SW14.2
unnamed: H2-D15.2 (A), H2-SW15.2
unnamed: H2-D16.2 (A), H2-SW16.2
unnamed: H2-D17.2 (A), H2-SW17.2
unnamed: H2-D18.2 (A), H2-SW18.2
unnamed: H2-D19.2 (A), H2-SW19.2
unnamed: H2-D20.2 (A), H2-SW20.2
unnamed: H2-D21.2 (A), H2-SW21.2
unnamed: H2-D22.2 (A), H2-SW22.2
unnamed: H2-D23.2 (A), H2-SW23.2
unnamed: H2-D24.2 (A), H2-SW24.2
unnamed: H2-D25.2 (A), H2-SW25.2
unnamed: H2-D26.2 (A), H2-SW26.2
unnamed: H2-D27.2 (A), H2-SW27.2
unnamed: H2-D28.2 (A), H2-SW28.2
unnamed: H2-D29.2 (A), H2-SW29.2
unnamed: H2-D30.2 (A), H2-SW30.2
unnamed: H2-DL1.2 (A), H2-L1.3, H2-L1.6 (3)
unnamed: H2-DL2.2 (A), H2-L2.3, H2-L2.6 (3)
unnamed: H2-DL3.2 (A), H2-L3.3, H2-L3.6 (3)
unnamed: H2-DRE1.2 (A), H2-RE1.E1 (SO)
unnamed: H2-DRE2.2 (A), H2-RE2.E1 (SO)
unnamed: H2-RE1.A1 (A), R5.2, R6.2
unnamed: H2-RE1.B1 (B), R7.2, R8.2
unnamed: H2-RE2.A1 (A), R13.2, R14.1
unnamed: H2-RE2.B1 (B), R15.1, R16.2
unnamed: H2-RE3.A1 (A), R37.2, R38.2
unnamed: H2-RE3.B1 (B), R39.2, R40.1
unnamed: C44.2, IC1.11 (VCC)
unnamed: Q1.4 (G), R44.2, R48.1
unnamed: R48.2, SW83.2 (B), SW83.5 (B)
VCC: C46.1, IC2.19 (VCC), R52.2, R53.2
VRNTC: IC2.7 (VRNTC), R57.2
V_BUS: C43.1, C53.1, D0.5 (VBUS), IC2.2 (IN), J1.A4 (VBUS), J1.A9 (VBUS), J1.B4 (VBUS), J1.B9 (VBUS), U1.32 (VBUS)
V_IN_TPS: C41.2, C42.2, IC1.6 (EN), IC1.7 (VIN), L2.2, Q1.5 (D)
V_OUT_MP: C40.1, C54.1, IC2.13 (SYS), L1.1, Q1.1 (S), Q1.2 (S), Q1.3 (S), R44.1
V_REG0: C33.2, C36.2, C52.1, IC3.39 (VIO), IC4.39 (VIO), R1.1, R3.1, R5.1, R7.1, R9.1, R13.1, R15.2, R26.2, R33.1, R35.1, R37.1, R39.1, R58.1, R59.1, U1.28 (VDD)

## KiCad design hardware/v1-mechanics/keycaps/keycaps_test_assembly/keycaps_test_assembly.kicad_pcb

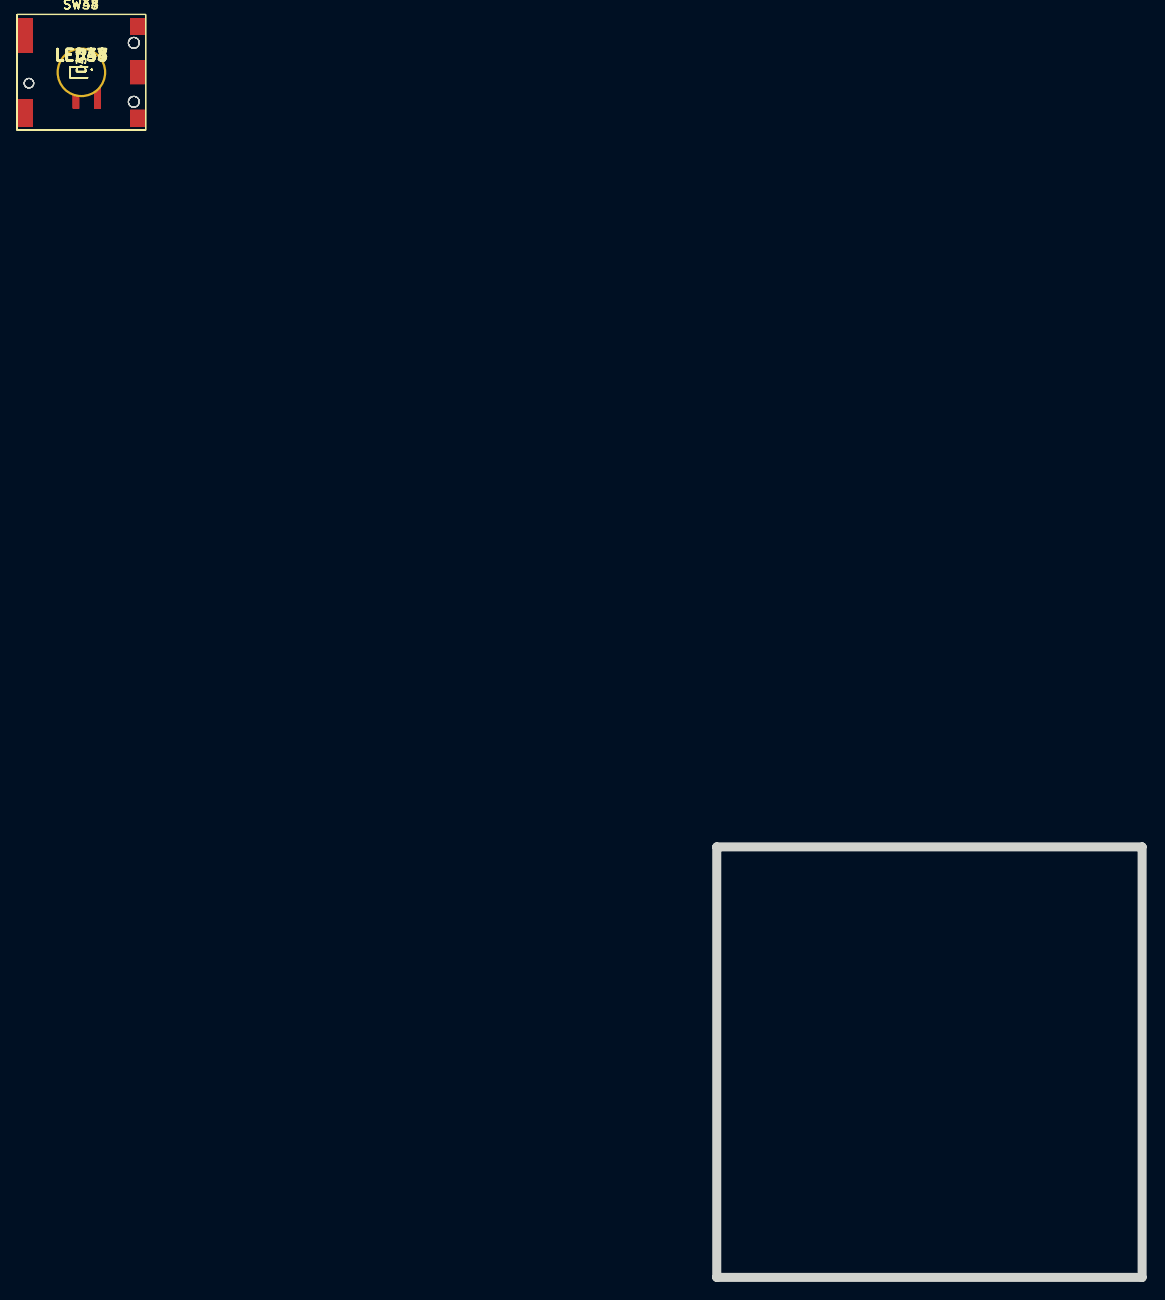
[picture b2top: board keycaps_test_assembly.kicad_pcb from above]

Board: 2 copper layers, 47.0 x 47.6 mm, 12 parts (0 on the bottom side), 14 nets, no tracks yet.

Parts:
D33, D34, D47, D48: D; D_SOD-523
LED33, LED34, LED47, LED48: LTST-FC12WEGBD-5A; LTSTFC12WEGBD5A
SW33, SW34, SW47, SW48: MSwitch; Cherry_ULP_SMD

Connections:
/LED Matricies/Chip1CurrentSource7: LED33.5 (ANODE), LED34.5 (ANODE)
/LED Matricies/Chip1CurrentSource9: LED47.5 (ANODE), LED48.5 (ANODE)
/LED Matricies/Chip1SinkSwitch5: LED34.1 (BLUE), LED47.1 (BLUE)
/LED Matricies/Chip1SinkSwitch6: LED34.2 (GREEN), LED47.2 (GREEN)
/LED Matricies/Chip1SinkSwitch7: LED34.3 (RED), LED47.3 (RED)
/LED Matricies/Chip1SinkSwitch8: LED34.4 (WHITE), LED47.4 (WHITE)
/MCU/Column5: SW33.1, SW47.1
/MCU/Column6: SW34.1, SW48.1
/MCU/Row3: D33.1 (K), D34.1 (K)
/MCU/Row4: D47.1 (K), D48.1 (K)
unnamed: D33.2 (A), SW33.2
unnamed: D34.2 (A), SW34.2
unnamed: D47.2 (A), SW47.2
unnamed: D48.2 (A), SW48.2

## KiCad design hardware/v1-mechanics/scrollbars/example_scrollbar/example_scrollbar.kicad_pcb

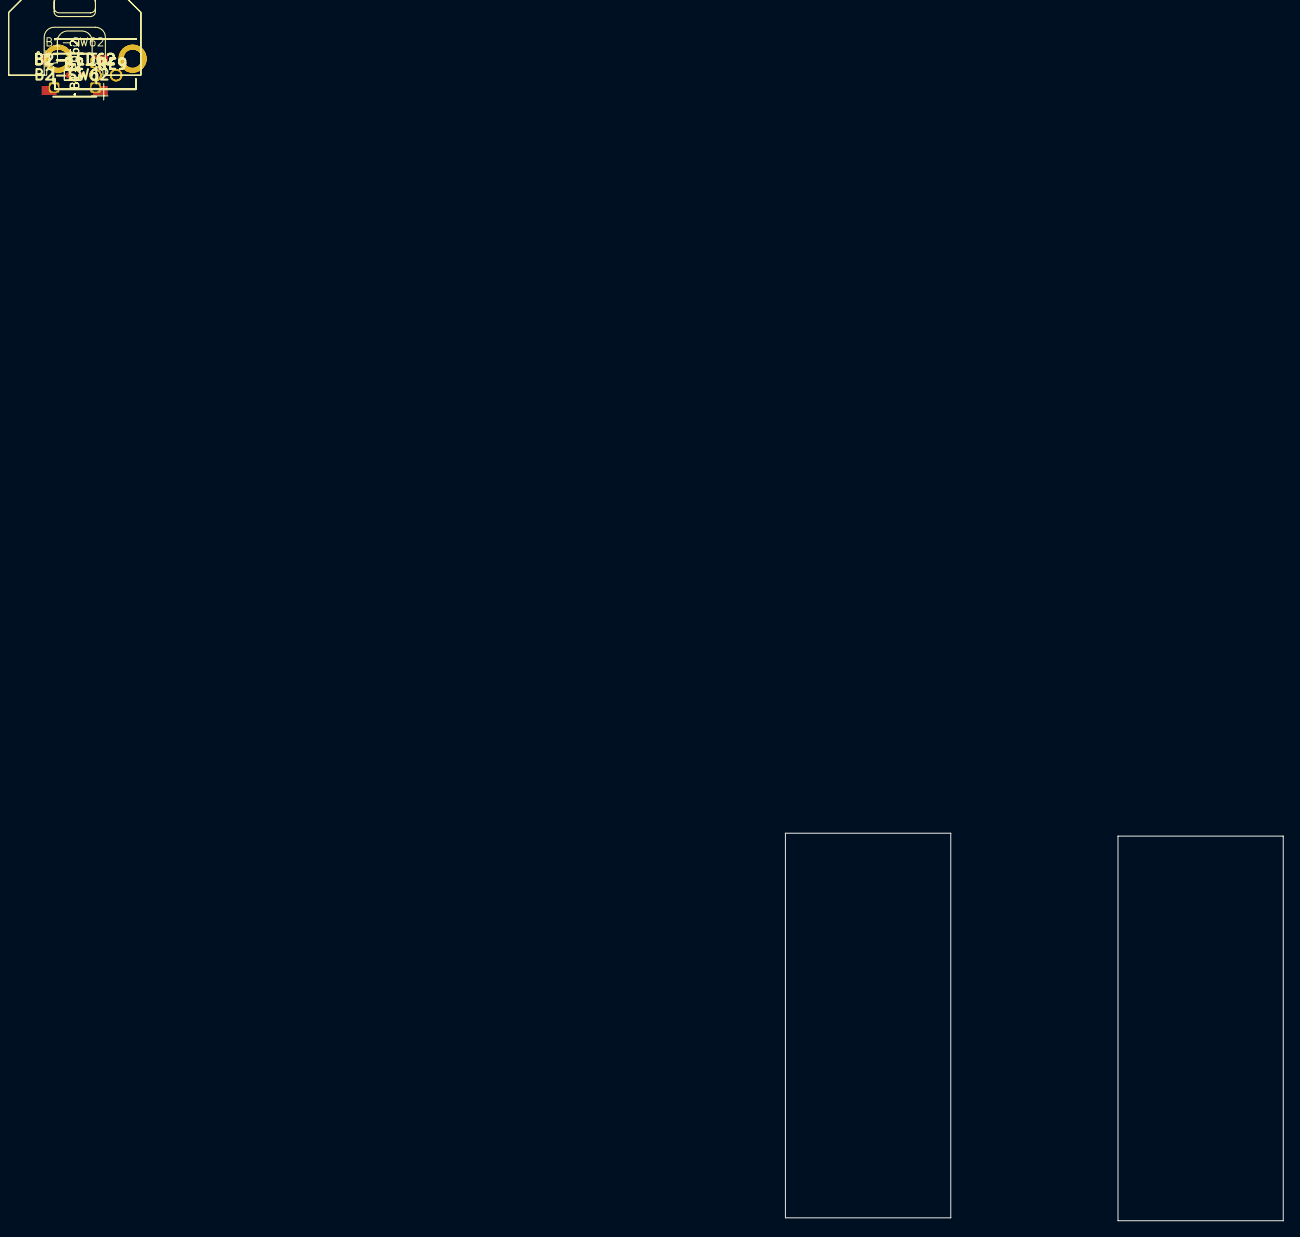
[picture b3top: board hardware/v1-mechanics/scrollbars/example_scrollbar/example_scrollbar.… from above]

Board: 2 copper layers, 10 parts (0 on the bottom side), 11 nets, no tracks yet.

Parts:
B1-D62, B2-D62: D; D_SOD-523
B1-LED62, B2-LED62: LTST-FC12WEGBD-5A; LTSTFC12WEGBD5A
B1-MP**: switched_grounded_scrollcap
B1-RE9, B2-RE9: EC10E1220505
B1-SW62: SW_Push; TC-1109-C-E
B2-MP**: grounded_scrollcap
B2-SW62: SW_Push; SKQGAKE010

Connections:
/LED Matricies/Chip1CurrentSource12: B1-LED62.5 (ANODE), B2-LED62.5 (ANODE)
/LED Matricies/Chip1SinkSwitch1: B1-LED62.1 (BLUE), B2-LED62.1 (BLUE)
/LED Matricies/Chip1SinkSwitch2: B1-LED62.2 (GREEN), B2-LED62.2 (GREEN)
/LED Matricies/Chip1SinkSwitch3: B1-LED62.3 (RED), B2-LED62.3 (RED)
/LED Matricies/Chip1SinkSwitch4: B1-LED62.4 (WHITE), B2-LED62.4 (WHITE)
/MCU/Column7: B1-SW62.1, B2-SW62.1 (1_1), B2-SW62.4 (1_1)
/MCU/Row5: B1-D62.1 (K), B2-D62.1 (K)
DGND: B1-RE9.C1 (C), B1-RE9.MH1 (H), B1-RE9.MH2 (H), B2-RE9.C1 (C), B2-RE9.MH1 (H), B2-RE9.MH2 (H)
unnamed: B1-D62.2 (A), B1-SW62.2, B2-D62.2 (A), B2-SW62.2 (2_2), B2-SW62.3 (2_2)
unnamed: B1-RE9.A1 (A), B2-RE9.A1 (A)
unnamed: B1-RE9.B1 (B), B2-RE9.B1 (B)

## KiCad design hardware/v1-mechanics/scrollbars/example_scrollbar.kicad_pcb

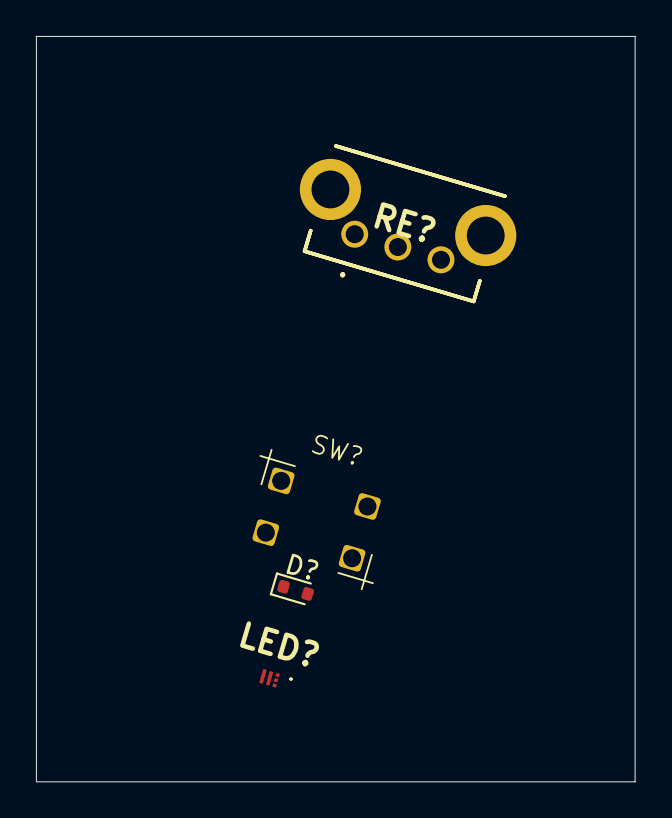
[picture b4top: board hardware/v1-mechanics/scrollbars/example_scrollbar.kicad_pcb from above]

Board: 2 copper layers, 33.3 x 41.4 mm, 4 parts (0 on the bottom side), 2 nets, no tracks yet.

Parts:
D?: D; D_SOD-523
LED?: LTST-FC12WEGBD-5A; LTSTFC12WEGBD5A
RE?: EC10E1220505
SW?: SW_Push; TC-1109-C-E

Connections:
DGND: RE?.C1 (C), RE?.MH1 (H), RE?.MH2 (H)
unnamed: D?.2 (A), SW?.2
